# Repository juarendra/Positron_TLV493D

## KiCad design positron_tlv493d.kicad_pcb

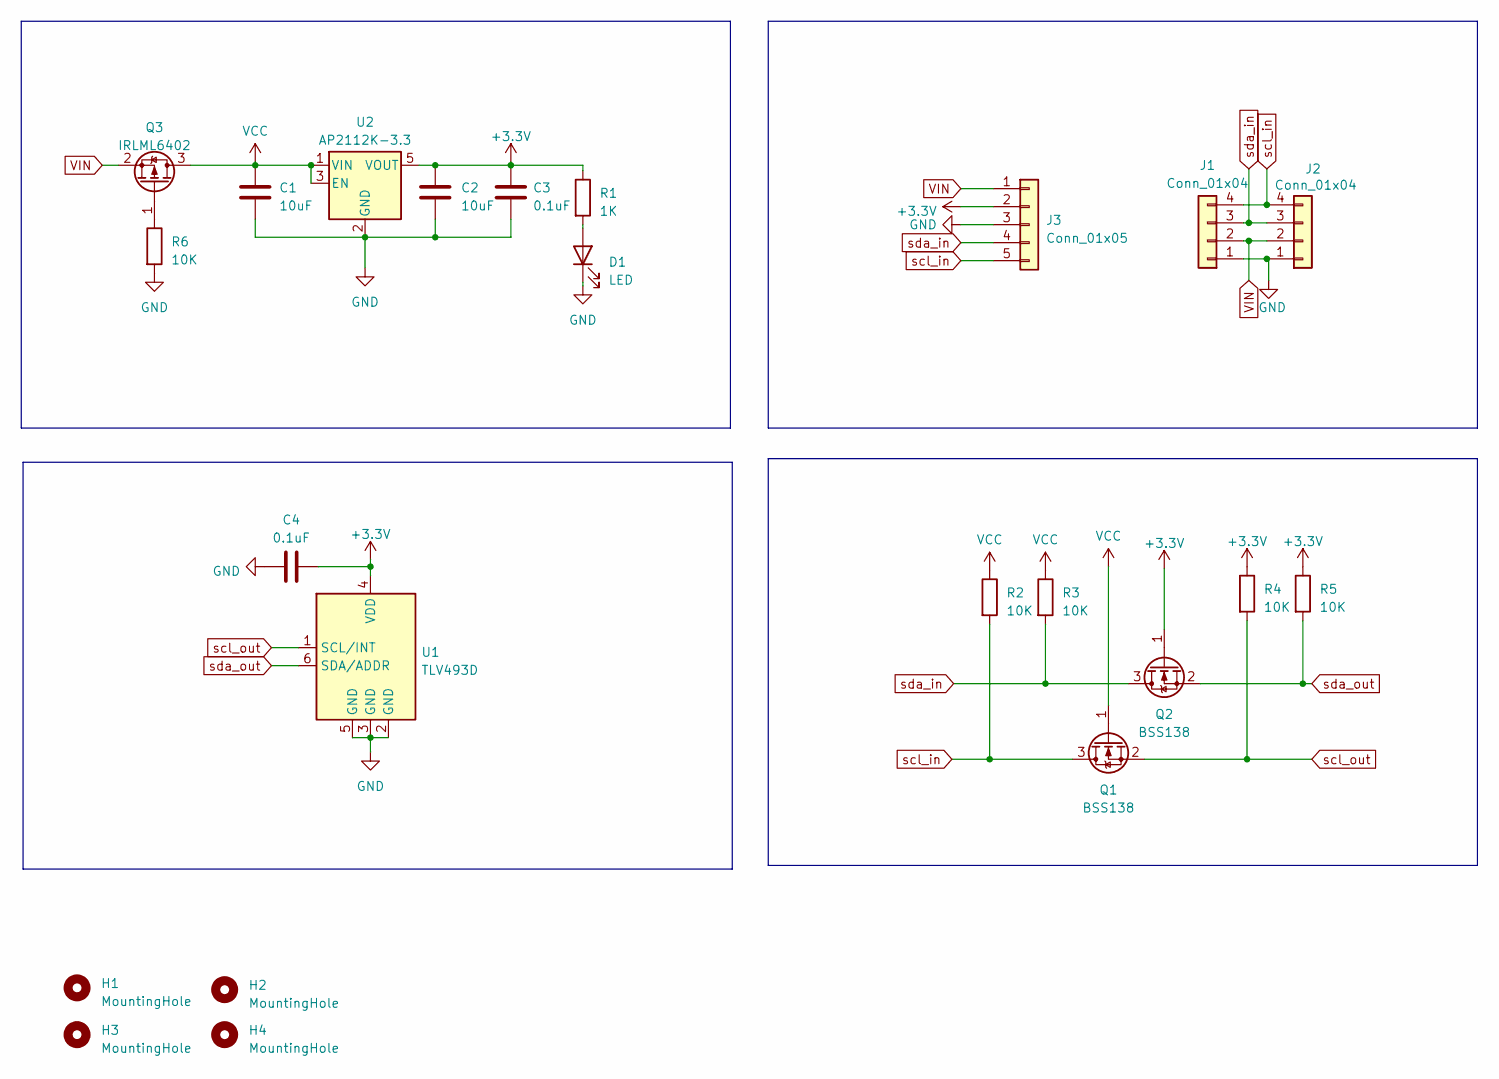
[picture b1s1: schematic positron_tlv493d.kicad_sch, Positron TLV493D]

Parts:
C1, C2: 10uF; C_0603_1608Metric
C3, C4: 0.1uF; C_0603_1608Metric
D1: LED; LED_0603_1608Metric
H1, H2, H3, H4: MountingHole; MountingHole_2.1mm
J1, J2: Conn_01x04; JST_SH_BM04B-SRSS-TB_1x04-1MP_P1.00mm_Vertical
J3: Conn_01x05; PinHeader_1x05_P2.54mm_Vertical
Q1, Q2: BSS138; SOT-23
Q3: IRLML6402; SOT-23
R1: 1K; R_0603_1608Metric
R2, R3, R4, R5, R6: 10K; R_0603_1608Metric
U1: TLV493D; SOT-23-6_Handsoldering
U2: AP2112K-3.3; SOT-23-5

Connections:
+3.3V: C2.1, C3.1, C4.2, J3.2, Q2.1 (G), R1.1, R4.1, R5.1, U1.4 (VDD), U2.5 (VOUT)
GND: C1.2, C2.2, C3.2, C4.1, D1.1 (K), J1.1, J2.1, J3.3, R6.2, U1.2 (GND), U1.3 (GND), U1.5 (GND), U2.2 (GND)
unnamed: D1.2 (A), R1.2
unnamed: Q3.1 (G), R6.1
VCC: C1.1, Q1.1 (G), Q3.3 (D), R2.1, R3.1, U2.1 (VIN), U2.3 (EN)
VIN: J1.2, J2.2, J3.1, Q3.2 (S)
scl_in: J1.4, J2.4, J3.5, Q1.3 (D), R2.2
scl_out: Q1.2 (S), R4.2, U1.1 (SCL/INT)
sda_in: J1.3, J2.3, J3.4, Q2.3 (D), R3.2
sda_out: Q2.2 (S), R5.2, U1.6 (SDA/ADDR)

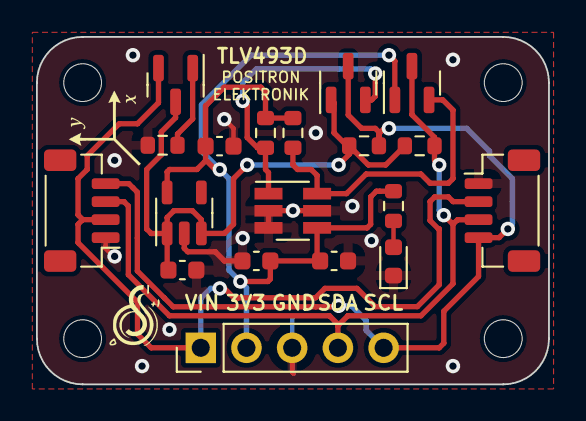
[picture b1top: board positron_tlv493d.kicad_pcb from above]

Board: 2 copper layers, 28.4 x 19.3 mm, 23 parts (0 on the bottom side), 10 nets.

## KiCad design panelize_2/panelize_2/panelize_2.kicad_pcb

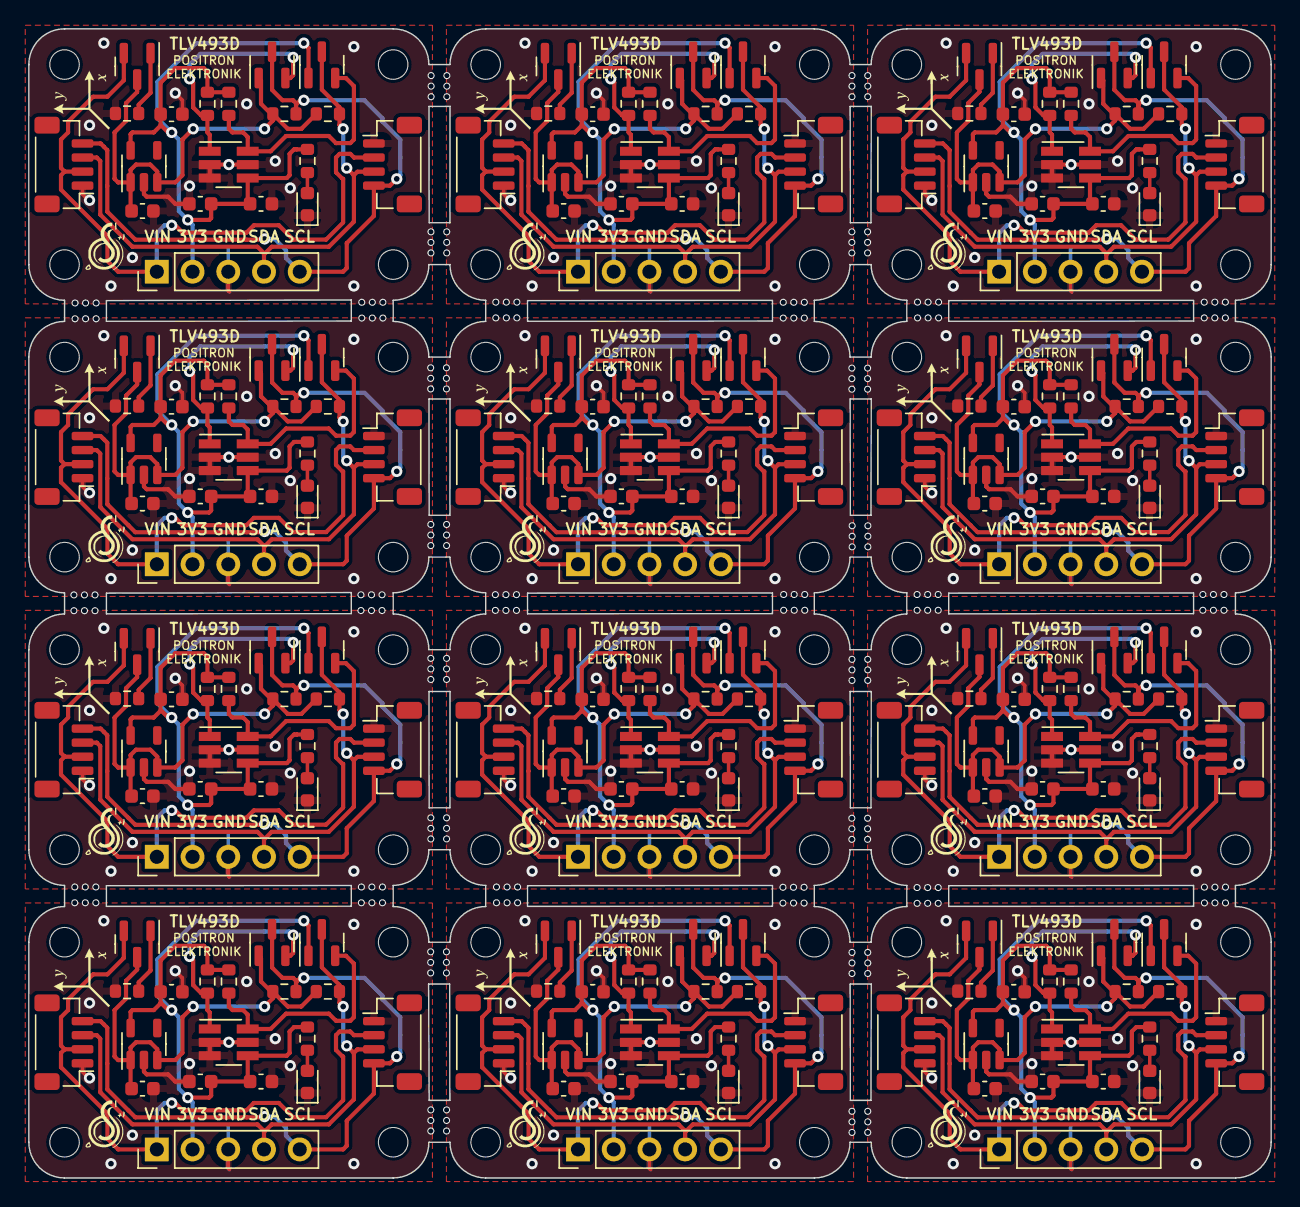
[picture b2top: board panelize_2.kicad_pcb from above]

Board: 2 copper layers, 88.3 x 81.7 mm, 276 parts (0 on the bottom side), 10 nets.

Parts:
C1, C2, C5, C6, C9, C10, C13, C14, C17, C18, C21, C22, C25, C26, C29, C30, C33, C34, C37, C38, C41, C42, C45, C46: 10uF; C_0603_1608Metric
C3, C4, C7, C8, C11, C12, C15, C16, C19, C20, C23, C24, C27, C28, C31, C32, C35, C36, C39, C40, C43, C44, C47, C48: 0.1uF; C_0603_1608Metric
D1, D2, D3, D4, D5, D6, D7, D8, D9, D10, D11, D12: LED; LED_0603_1608Metric
H1, H2, H3, H4, H5, H6, H7, H8, H9, H10, H11, H12, H13, H14, H15, H16, H17, H18, H19, H20, H21, H22, H23, H24, H25, H26, H27, H28, H29, H30, H31, H32, H33, H34, H35, H36, H37, H38, H39, H40, H41, H42, H43, H44, H45, H46, H47, H48: MountingHole; MountingHole_2.1mm
J1, J2, J4, J5, J7, J8, J10, J11, J13, J14, J16, J17, J19, J20, J22, J23, J25, J26, J28, J29, J31, J32, J34, J35: Conn_01x04; JST_SH_BM04B-SRSS-TB_1x04-1MP_P1.00mm_Vertical
J3, J6, J9, J12, J15, J18, J21, J24, J27, J30, J33, J36: Conn_01x05; PinHeader_1x05_P2.54mm_Vertical
Q1, Q2, Q4, Q5, Q7, Q8, Q10, Q11, Q13, Q14, Q16, Q17, Q19, Q20, Q22, Q23, Q25, Q26, Q28, Q29, Q31, Q32, Q34, Q35: BSS138; SOT-23
Q3, Q6, Q9, Q12, Q15, Q18, Q21, Q24, Q27, Q30, Q33, Q36: IRLML6402; SOT-23
R1, R7, R13, R19, R25, R31, R37, R43, R49, R55, R61, R67: 1K; R_0603_1608Metric
R2, R3, R4, R5, R6, R8, R9, R10, R11, R12, R14, R15, R16, R17, R18, R20, R21, R22, R23, R24, R26, R27, R28, R29, R30, R32, R33, R34, R35, R36, R38, R39, R40, R41, R42, R44, R45, R46, R47, R48, R50, R51, R52, R53, R54, R56, R57, R58, R59, R60, R62, R63, R64, R65, R66, R68, R69, R70, R71, R72: 10K; R_0603_1608Metric
U1, U3, U5, U7, U9, U11, U13, U15, U17, U19, U21, U23: TLV493D; SOT-23-6_Handsoldering
U2, U4, U6, U8, U10, U12, U14, U16, U18, U20, U22, U24: AP2112K-3.3; SOT-23-5

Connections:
+3.3V: C2.1, C3.1, C4.2, C6.1, C7.1, C8.2, C10.1, C11.1, C12.2, C14.1, C15.1, C16.2, C18.1, C19.1, C20.2, C22.1, C23.1, C24.2, C26.1, C27.1, C28.2, C30.1, C31.1, C32.2, C34.1, C35.1, C36.2, C38.1, C39.1, C40.2, C42.1, C43.1, C44.2, C46.1, C47.1, C48.2, J3.2, J6.2, J9.2, J12.2, J15.2, J18.2, J21.2, J24.2, J27.2, J30.2, J33.2, J36.2, Q2.1 (G), Q5.1 (G), Q8.1 (G), Q11.1 (G), Q14.1 (G), Q17.1 (G), Q20.1 (G), Q23.1 (G), Q26.1 (G), Q29.1 (G), Q32.1 (G), Q35.1 (G), R1.1, R4.1, R5.1, R7.1, R10.1, R11.1, R13.1, R16.1, R17.1, R19.1, R22.1, R23.1, R25.1, R28.1, R29.1, R31.1, R34.1, R35.1, R37.1, R40.1, R41.1, R43.1, R46.1, R47.1, R49.1, R52.1, R53.1, R55.1, R58.1, R59.1, R61.1, R64.1, R65.1, R67.1, R70.1, R71.1, U1.4 (VDD), U2.5 (VOUT), U3.4 (VDD), U4.5 (VOUT), U5.4 (VDD), U6.5 (VOUT), U7.4 (VDD), U8.5 (VOUT), U9.4 (VDD), U10.5 (VOUT), U11.4 (VDD), U12.5 (VOUT), U13.4 (VDD), U14.5 (VOUT), U15.4 (VDD), U16.5 (VOUT), U17.4 (VDD), U18.5 (VOUT), U19.4 (VDD), U20.5 (VOUT), U21.4 (VDD), U22.5 (VOUT), U23.4 (VDD), U24.5 (VOUT)
GND: C1.2, C2.2, C3.2, C4.1, C5.2, C6.2, C7.2, C8.1, C9.2, C10.2, C11.2, C12.1, C13.2, C14.2, C15.2, C16.1, C17.2, C18.2, C19.2, C20.1, C21.2, C22.2, C23.2, C24.1, C25.2, C26.2, C27.2, C28.1, C29.2, C30.2, C31.2, C32.1, C33.2, C34.2, C35.2, C36.1, C37.2, C38.2, C39.2, C40.1, C41.2, C42.2, C43.2, C44.1, C45.2, C46.2, C47.2, C48.1, D1.1 (K), D2.1 (K), D3.1 (K), D4.1 (K), D5.1 (K), D6.1 (K), D7.1 (K), D8.1 (K), D9.1 (K), D10.1 (K), D11.1 (K), D12.1 (K), J1.1, J2.1, J3.3, J4.1, J5.1, J6.3, J7.1, J8.1, J9.3, J10.1, J11.1, J12.3, J13.1, J14.1, J15.3, J16.1, J17.1, J18.3, J19.1, J20.1, J21.3, J22.1, J23.1, J24.3, J25.1, J26.1, J27.3, J28.1, J29.1, J30.3, J31.1, J32.1, J33.3, J34.1, J35.1, J36.3, R6.2, R12.2, R18.2, R24.2, R30.2, R36.2, R42.2, R48.2, R54.2, R60.2, R66.2, R72.2, U1.2 (GND), U1.3 (GND), U1.5 (GND), U2.2 (GND), U3.2 (GND), U3.3 (GND), U3.5 (GND), U4.2 (GND), U5.2 (GND), U5.3 (GND), U5.5 (GND), U6.2 (GND), U7.2 (GND), U7.3 (GND), U7.5 (GND), U8.2 (GND), U9.2 (GND), U9.3 (GND), U9.5 (GND), U10.2 (GND), U11.2 (GND), U11.3 (GND), U11.5 (GND), U12.2 (GND), U13.2 (GND), U13.3 (GND), U13.5 (GND), U14.2 (GND), U15.2 (GND), U15.3 (GND), U15.5 (GND), U16.2 (GND), U17.2 (GND), U17.3 (GND), U17.5 (GND), U18.2 (GND), U19.2 (GND), U19.3 (GND), U19.5 (GND), U20.2 (GND), U21.2 (GND), U21.3 (GND), U21.5 (GND), U22.2 (GND), U23.2 (GND), U23.3 (GND), U23.5 (GND), U24.2 (GND)
unnamed: D1.2 (A), D2.2 (A), D3.2 (A), D4.2 (A), D5.2 (A), D6.2 (A), D7.2 (A), D8.2 (A), D9.2 (A), D10.2 (A), D11.2 (A), D12.2 (A), R1.2, R7.2, R13.2, R19.2, R25.2, R31.2, R37.2, R43.2, R49.2, R55.2, R61.2, R67.2
unnamed: Q3.1 (G), Q6.1 (G), Q9.1 (G), Q12.1 (G), Q15.1 (G), Q18.1 (G), Q21.1 (G), Q24.1 (G), Q27.1 (G), Q30.1 (G), Q33.1 (G), Q36.1 (G), R6.1, R12.1, R18.1, R24.1, R30.1, R36.1, R42.1, R48.1, R54.1, R60.1, R66.1, R72.1
VCC: C1.1, C5.1, C9.1, C13.1, C17.1, C21.1, C25.1, C29.1, C33.1, C37.1, C41.1, C45.1, Q1.1 (G), Q3.3 (D), Q4.1 (G), Q6.3 (D), Q7.1 (G), Q9.3 (D), Q10.1 (G), Q12.3 (D), Q13.1 (G), Q15.3 (D), Q16.1 (G), Q18.3 (D), Q19.1 (G), Q21.3 (D), Q22.1 (G), Q24.3 (D), Q25.1 (G), Q27.3 (D), Q28.1 (G), Q30.3 (D), Q31.1 (G), Q33.3 (D), Q34.1 (G), Q36.3 (D), R2.1, R3.1, R8.1, R9.1, R14.1, R15.1, R20.1, R21.1, R26.1, R27.1, R32.1, R33.1, R38.1, R39.1, R44.1, R45.1, R50.1, R51.1, R56.1, R57.1, R62.1, R63.1, R68.1, R69.1, U2.1 (VIN), U2.3 (EN), U4.1 (VIN), U4.3 (EN), U6.1 (VIN), U6.3 (EN), U8.1 (VIN), U8.3 (EN), U10.1 (VIN), U10.3 (EN), U12.1 (VIN), U12.3 (EN), U14.1 (VIN), U14.3 (EN), U16.1 (VIN), U16.3 (EN), U18.1 (VIN), U18.3 (EN), U20.1 (VIN), U20.3 (EN), U22.1 (VIN), U22.3 (EN), U24.1 (VIN), U24.3 (EN)
VIN: J1.2, J2.2, J3.1, J4.2, J5.2, J6.1, J7.2, J8.2, J9.1, J10.2, J11.2, J12.1, J13.2, J14.2, J15.1, J16.2, J17.2, J18.1, J19.2, J20.2, J21.1, J22.2, J23.2, J24.1, J25.2, J26.2, J27.1, J28.2, J29.2, J30.1, J31.2, J32.2, J33.1, J34.2, J35.2, J36.1, Q3.2 (S), Q6.2 (S), Q9.2 (S), Q12.2 (S), Q15.2 (S), Q18.2 (S), Q21.2 (S), Q24.2 (S), Q27.2 (S), Q30.2 (S), Q33.2 (S), Q36.2 (S)
scl_in: J1.4, J2.4, J3.5, J4.4, J5.4, J6.5, J7.4, J8.4, J9.5, J10.4, J11.4, J12.5, J13.4, J14.4, J15.5, J16.4, J17.4, J18.5, J19.4, J20.4, J21.5, J22.4, J23.4, J24.5, J25.4, J26.4, J27.5, J28.4, J29.4, J30.5, J31.4, J32.4, J33.5, J34.4, J35.4, J36.5, Q1.3 (D), Q4.3 (D), Q7.3 (D), Q10.3 (D), Q13.3 (D), Q16.3 (D), Q19.3 (D), Q22.3 (D), Q25.3 (D), Q28.3 (D), Q31.3 (D), Q34.3 (D), R2.2, R8.2, R14.2, R20.2, R26.2, R32.2, R38.2, R44.2, R50.2, R56.2, R62.2, R68.2
scl_out: Q1.2 (S), Q4.2 (S), Q7.2 (S), Q10.2 (S), Q13.2 (S), Q16.2 (S), Q19.2 (S), Q22.2 (S), Q25.2 (S), Q28.2 (S), Q31.2 (S), Q34.2 (S), R4.2, R10.2, R16.2, R22.2, R28.2, R34.2, R40.2, R46.2, R52.2, R58.2, R64.2, R70.2, U1.1 (SCL/INT), U3.1 (SCL/INT), U5.1 (SCL/INT), U7.1 (SCL/INT), U9.1 (SCL/INT), U11.1 (SCL/INT), U13.1 (SCL/INT), U15.1 (SCL/INT), U17.1 (SCL/INT), U19.1 (SCL/INT), U21.1 (SCL/INT), U23.1 (SCL/INT)
sda_in: J1.3, J2.3, J3.4, J4.3, J5.3, J6.4, J7.3, J8.3, J9.4, J10.3, J11.3, J12.4, J13.3, J14.3, J15.4, J16.3, J17.3, J18.4, J19.3, J20.3, J21.4, J22.3, J23.3, J24.4, J25.3, J26.3, J27.4, J28.3, J29.3, J30.4, J31.3, J32.3, J33.4, J34.3, J35.3, J36.4, Q2.3 (D), Q5.3 (D), Q8.3 (D), Q11.3 (D), Q14.3 (D), Q17.3 (D), Q20.3 (D), Q23.3 (D), Q26.3 (D), Q29.3 (D), Q32.3 (D), Q35.3 (D), R3.2, R9.2, R15.2, R21.2, R27.2, R33.2, R39.2, R45.2, R51.2, R57.2, R63.2, R69.2
sda_out: Q2.2 (S), Q5.2 (S), Q8.2 (S), Q11.2 (S), Q14.2 (S), Q17.2 (S), Q20.2 (S), Q23.2 (S), Q26.2 (S), Q29.2 (S), Q32.2 (S), Q35.2 (S), R5.2, R11.2, R17.2, R23.2, R29.2, R35.2, R41.2, R47.2, R53.2, R59.2, R65.2, R71.2, U1.6 (SDA/ADDR), U3.6 (SDA/ADDR), U5.6 (SDA/ADDR), U7.6 (SDA/ADDR), U9.6 (SDA/ADDR), U11.6 (SDA/ADDR), U13.6 (SDA/ADDR), U15.6 (SDA/ADDR), U17.6 (SDA/ADDR), U19.6 (SDA/ADDR), U21.6 (SDA/ADDR), U23.6 (SDA/ADDR)

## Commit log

2025-06-26 FEAT :update pcb
